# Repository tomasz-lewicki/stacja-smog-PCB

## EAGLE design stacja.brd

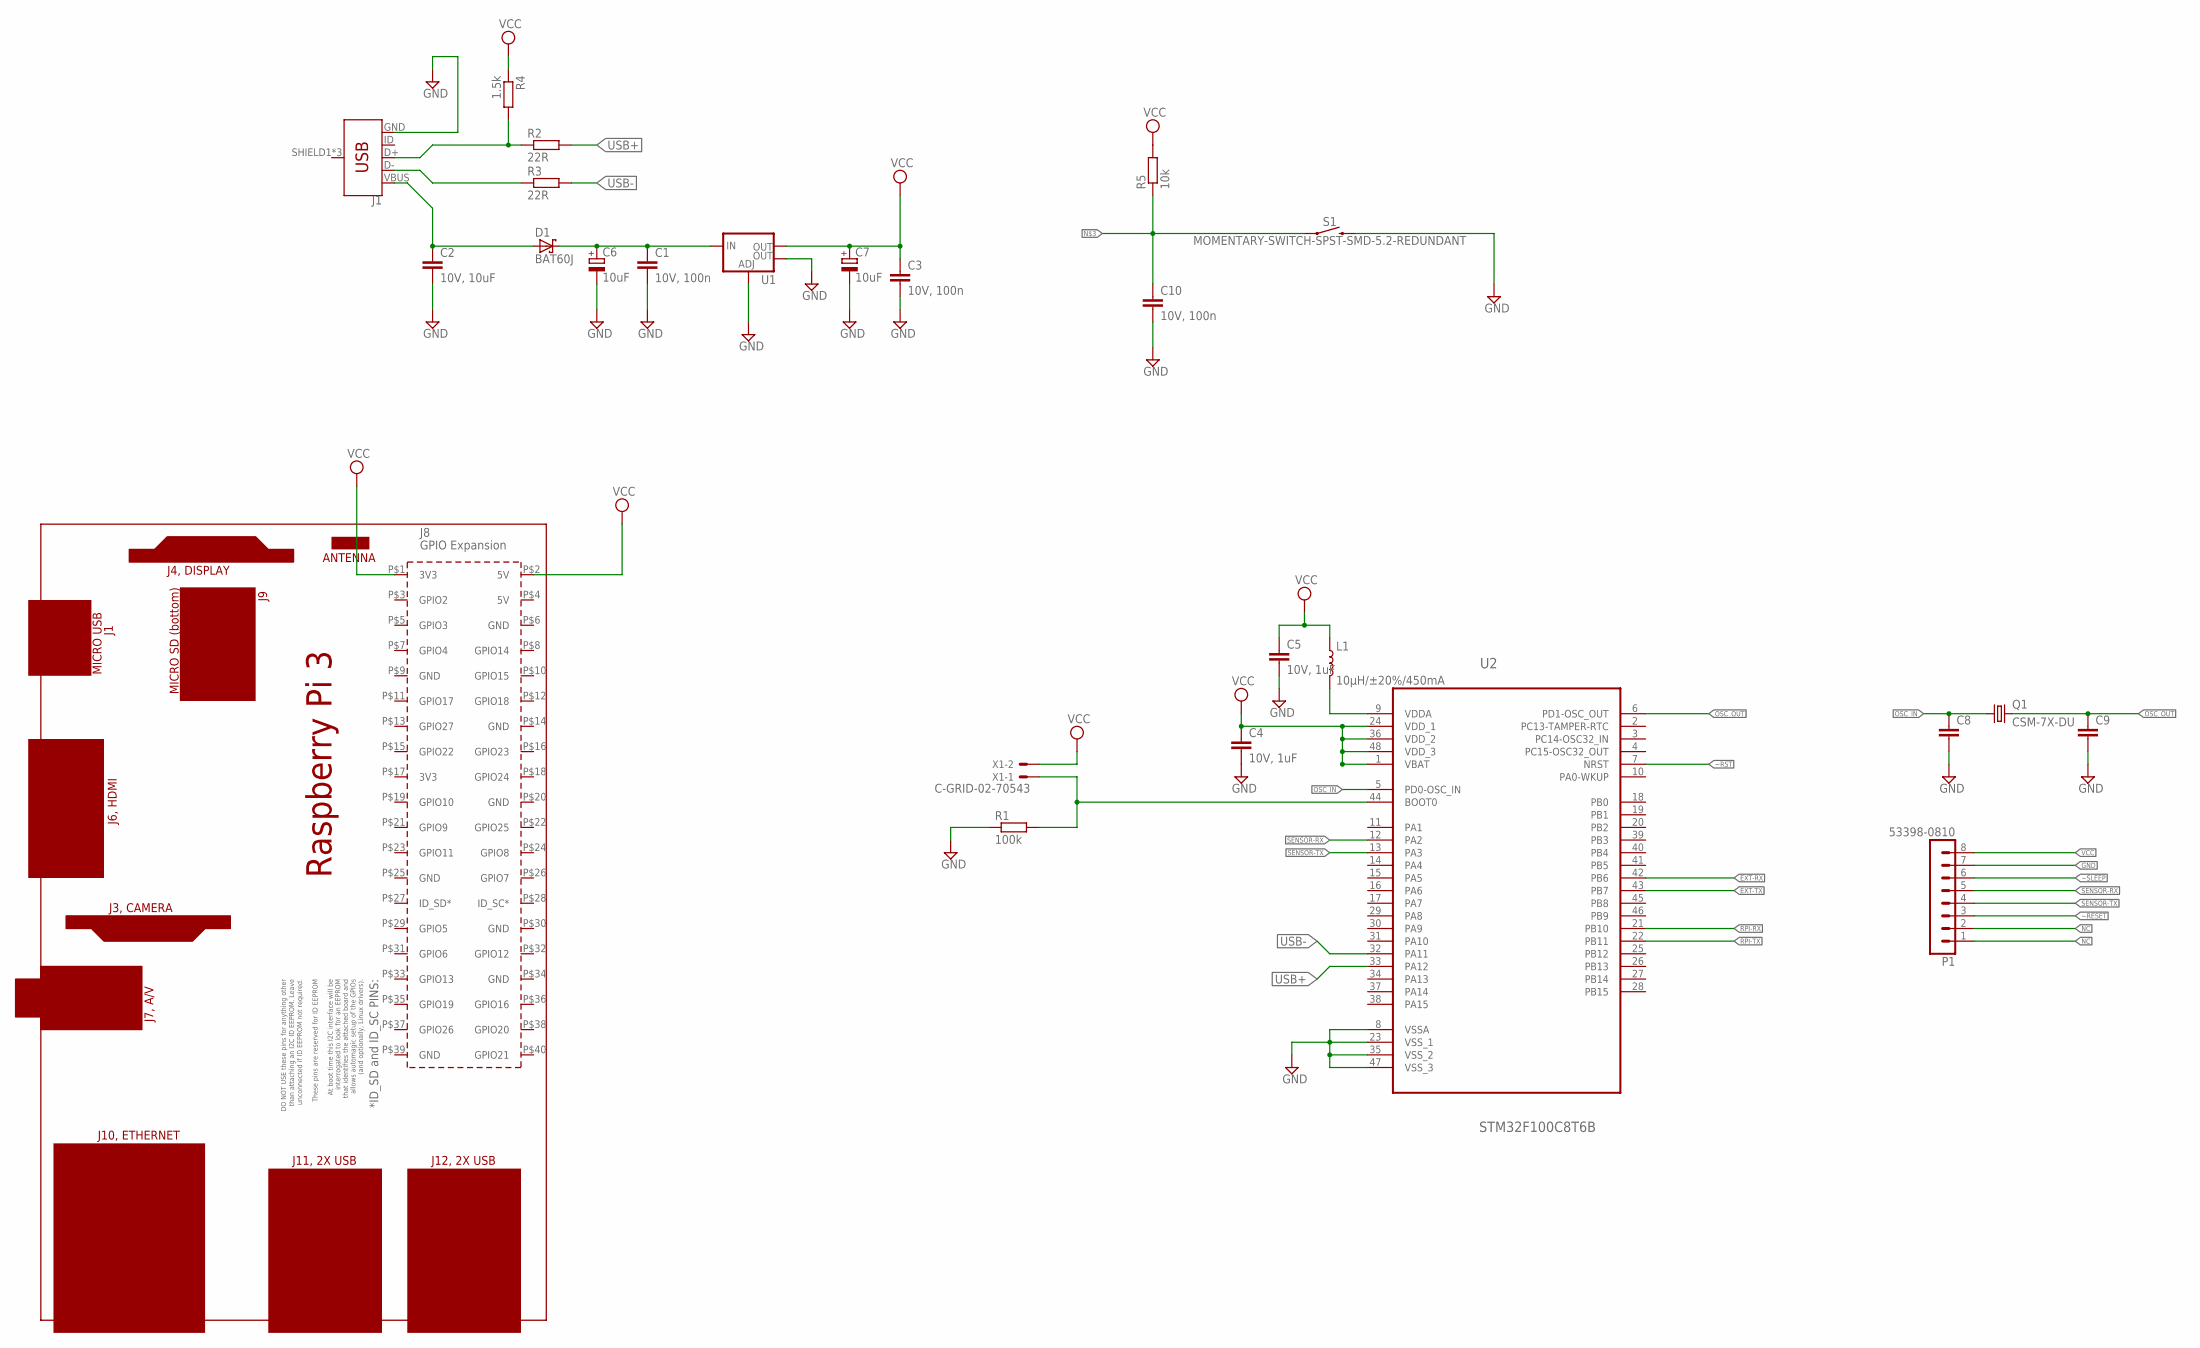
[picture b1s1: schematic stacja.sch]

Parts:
C1, C3, C10: 10V, 100n; C0805K
C2: 10V, 10uF; C0805K
C4, C5: 10V, 1uF; C0805K
C6, C7: 10uF; SANYO-OSCON_SMD_B6
C8, C9: C-EUC0805K; C0805K
D1: BAT60J; SOD323_ST
J1: USB_MICRO-B_FEMALE-SMT; USB-B-MICRO-SMD
L1: 10µH/±20%/450mA; 0805
P1: 53398-0810
PCB1: RPI3
Q1: CSM-7X-DU
R1: 100k; R0805
R2, R3: 22R; R0805
R4: 1.5k; R0805
R5: 10k; R0805
S1: MOMENTARY-SWITCH-SPST-SMD-5.2-REDUNDANT; TACTILE_SWITCH_SMD_5.2MM
U1: V_REG_LM1117SOT223; SOT223
U2: STM32F100C8T6B; QFP50P900X900X160-48N
X1: C-GRID-02-70543; 70543-02

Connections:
EXT-RX: U2.42 (PB6)
EXT-TX: U2.43 (PB7)
GND: C1.2, C2.2, C3.2, C4.2, C5.2, C6.-, C7.-, C8.2, C9.2, C10.2, J1.GND, P1.7, R1.1, S1.3 (2), S1.4 (2), U1.1 (ADJ), U1.4 (OUT), U2.8 (VSSA), U2.23 (VSS_1), U2.35 (VSS_2), U2.47 (VSS_3)
unnamed: R1.2, U2.44 (BOOT0), X1.1
unnamed: L1.2, U2.9 (VDDA)
unnamed: C10.1, R5.1, S1.1, S1.2 (1)
unnamed: J1.D+, R2.1, R4.2
unnamed: J1.D-, R3.1
unnamed: C1.1, C6.+, D1.C, U1.3 (IN)
unnamed: C2.1, D1.A, J1.VBUS
NC: P1.1, P1.2
OSC_IN: C8.1, Q1.1, U2.5 (PD0-OSC_IN)
OSC_OUT: C9.1, Q1.2, U2.6 (PD1-OSC_OUT)
RPI-RX: U2.21 (PB10)
RPI-TX: U2.22 (PB11)
SENSOR-RX: P1.5, U2.12 (PA2)
SENSOR-TX: P1.4, U2.13 (PA3)
USB+: R2.2, U2.33 (PA12)
USB-: R3.2, U2.32 (PA11)
VCC: C3.1, C4.1, C5.1, C7.+, L1.1, P1.8, PCB1.P$1 (3V3), PCB1.P$2 (5V), R4.1, R5.2, U1.2 (OUT), U2.1 (VBAT), U2.24 (VDD_1), U2.36 (VDD_2), U2.48 (VDD_3), X1.2
~RESET: P1.3
~RST: U2.7 (NRST)
~SLEEP: P1.6

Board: 2 copper layers, 25 parts (0 on the bottom side), 16 nets, no tracks yet.

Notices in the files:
parts and their libraries:
molex-pico: Copyright (C) 2010, Bob Starr
SparkFun-Connectors: Licensing: Creative Commons ShareAlike 4.0 International - https://creativecommons.org/licenses/by-sa/4.0
